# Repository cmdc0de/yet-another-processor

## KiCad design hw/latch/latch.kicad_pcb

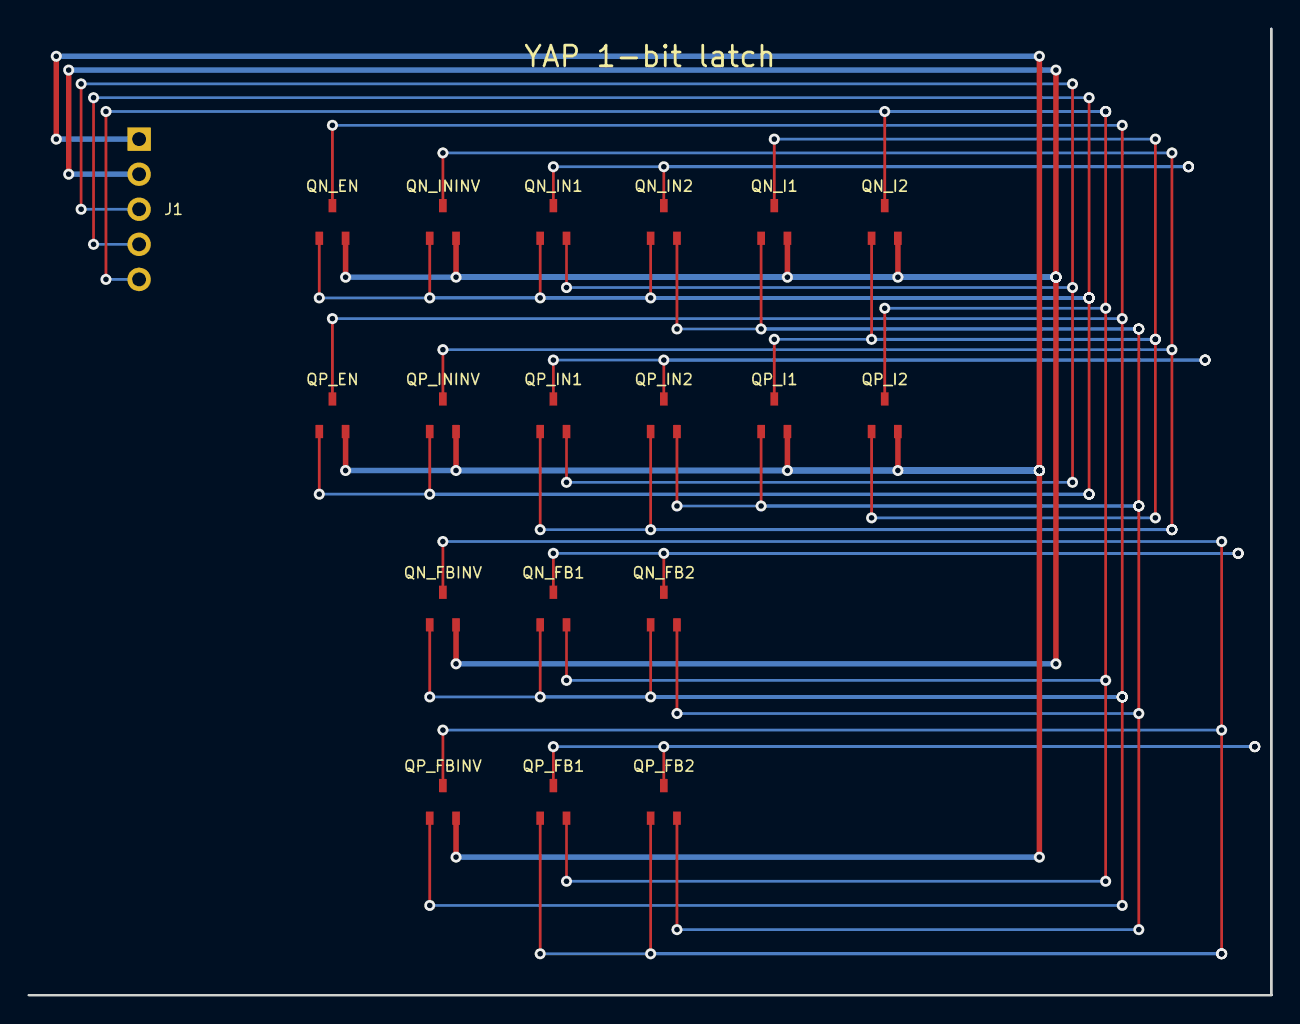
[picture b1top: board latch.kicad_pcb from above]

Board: 2 copper layers, 90.0 x 70.0 mm, 19 parts (0 on the bottom side), 14 nets.

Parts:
J1: HDR_2.54_1x05; PinHeader_1x05_P2.54mm
QN_EN: IRLML6246; MICRO3_SOT23_INF
QN_FB1, QN_FB2: IRLML6246; MICRO3_SOT23_INF
QN_FBINV: IRLML6246; MICRO3_SOT23_INF
QN_I1, QN_I2: IRLML6246; MICRO3_SOT23_INF
QN_IN1, QN_IN2: IRLML6246; MICRO3_SOT23_INF
QN_ININV: IRLML6246; MICRO3_SOT23_INF
QP_EN: IRLML6401; MICRO3_SOT23_INF
QP_FB1, QP_FB2: IRLML6401; MICRO3_SOT23_INF
QP_FBINV: IRLML6401; MICRO3_SOT23_INF
QP_I1, QP_I2: IRLML6401; MICRO3_SOT23_INF
QP_IN1, QP_IN2: IRLML6401; MICRO3_SOT23_INF
QP_ININV: IRLML6401; MICRO3_SOT23_INF

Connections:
D: J1.3, QN_IN1.2, QP_IN1.2
EN: J1.4, QN_EN.1, QN_IN1.1, QN_IN2.1, QN_ININV.1, QP_EN.1, QP_ININV.1
ENB: QN_EN.3, QN_FB1.1, QN_FB2.1, QN_FBINV.1, QP_EN.3, QP_FBINV.1
ENB_FB: QN_FBINV.3, QP_FB1.1, QP_FB2.1, QP_FBINV.3
ENB_IN: QN_ININV.3, QP_IN1.1, QP_IN2.1, QP_ININV.3
MIDN_FB: QN_FB1.3, QN_FB2.3
MIDN_IN: QN_IN1.3, QN_IN2.3
MIDP_FB: QP_FB1.3, QP_FB2.3
MIDP_IN: QP_IN1.3, QP_IN2.3
N1: QN_FB2.2, QN_I1.1, QN_IN2.2, QP_FB2.2, QP_I1.1, QP_IN2.2
Q: J1.5, QN_FB1.2, QN_I2.3, QP_FB1.2, QP_I2.3
QB: QN_I1.3, QN_I2.1, QP_I1.3, QP_I2.1
VDD: J1.1, QP_EN.2, QP_FBINV.2, QP_I1.2, QP_I2.2, QP_ININV.2
VSS: J1.2, QN_EN.2, QN_FBINV.2, QN_I1.2, QN_I2.2, QN_ININV.2

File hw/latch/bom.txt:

YAP 1-bit latch BOM (PHYSICAL-CPU-017)
Board: hw/latch/latch.kicad_pcb

Qty  Part         Package                         Ref / notes
9    IRLML6246    SOT-23 MICRO3_SOT23_INF         QN_* (see assembly.md)
9    IRLML6401    SOT-23 MICRO3_SOT23_INF         QP_* (see assembly.md)
1    PinHeader    2.54 mm 1x05                    J1 pins VDD, VSS, D, EN, Q

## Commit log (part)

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2025-11-24 initial ltspice files for a 1 bit adder
2025-11-29 Ok switched all mosfets to be IRML6246 n channel and IRML4601 for p channel and switched to max 4610CSD part since I'll be using NO switches
2025-11-29 line ending .....
2025-11-29 updated library
